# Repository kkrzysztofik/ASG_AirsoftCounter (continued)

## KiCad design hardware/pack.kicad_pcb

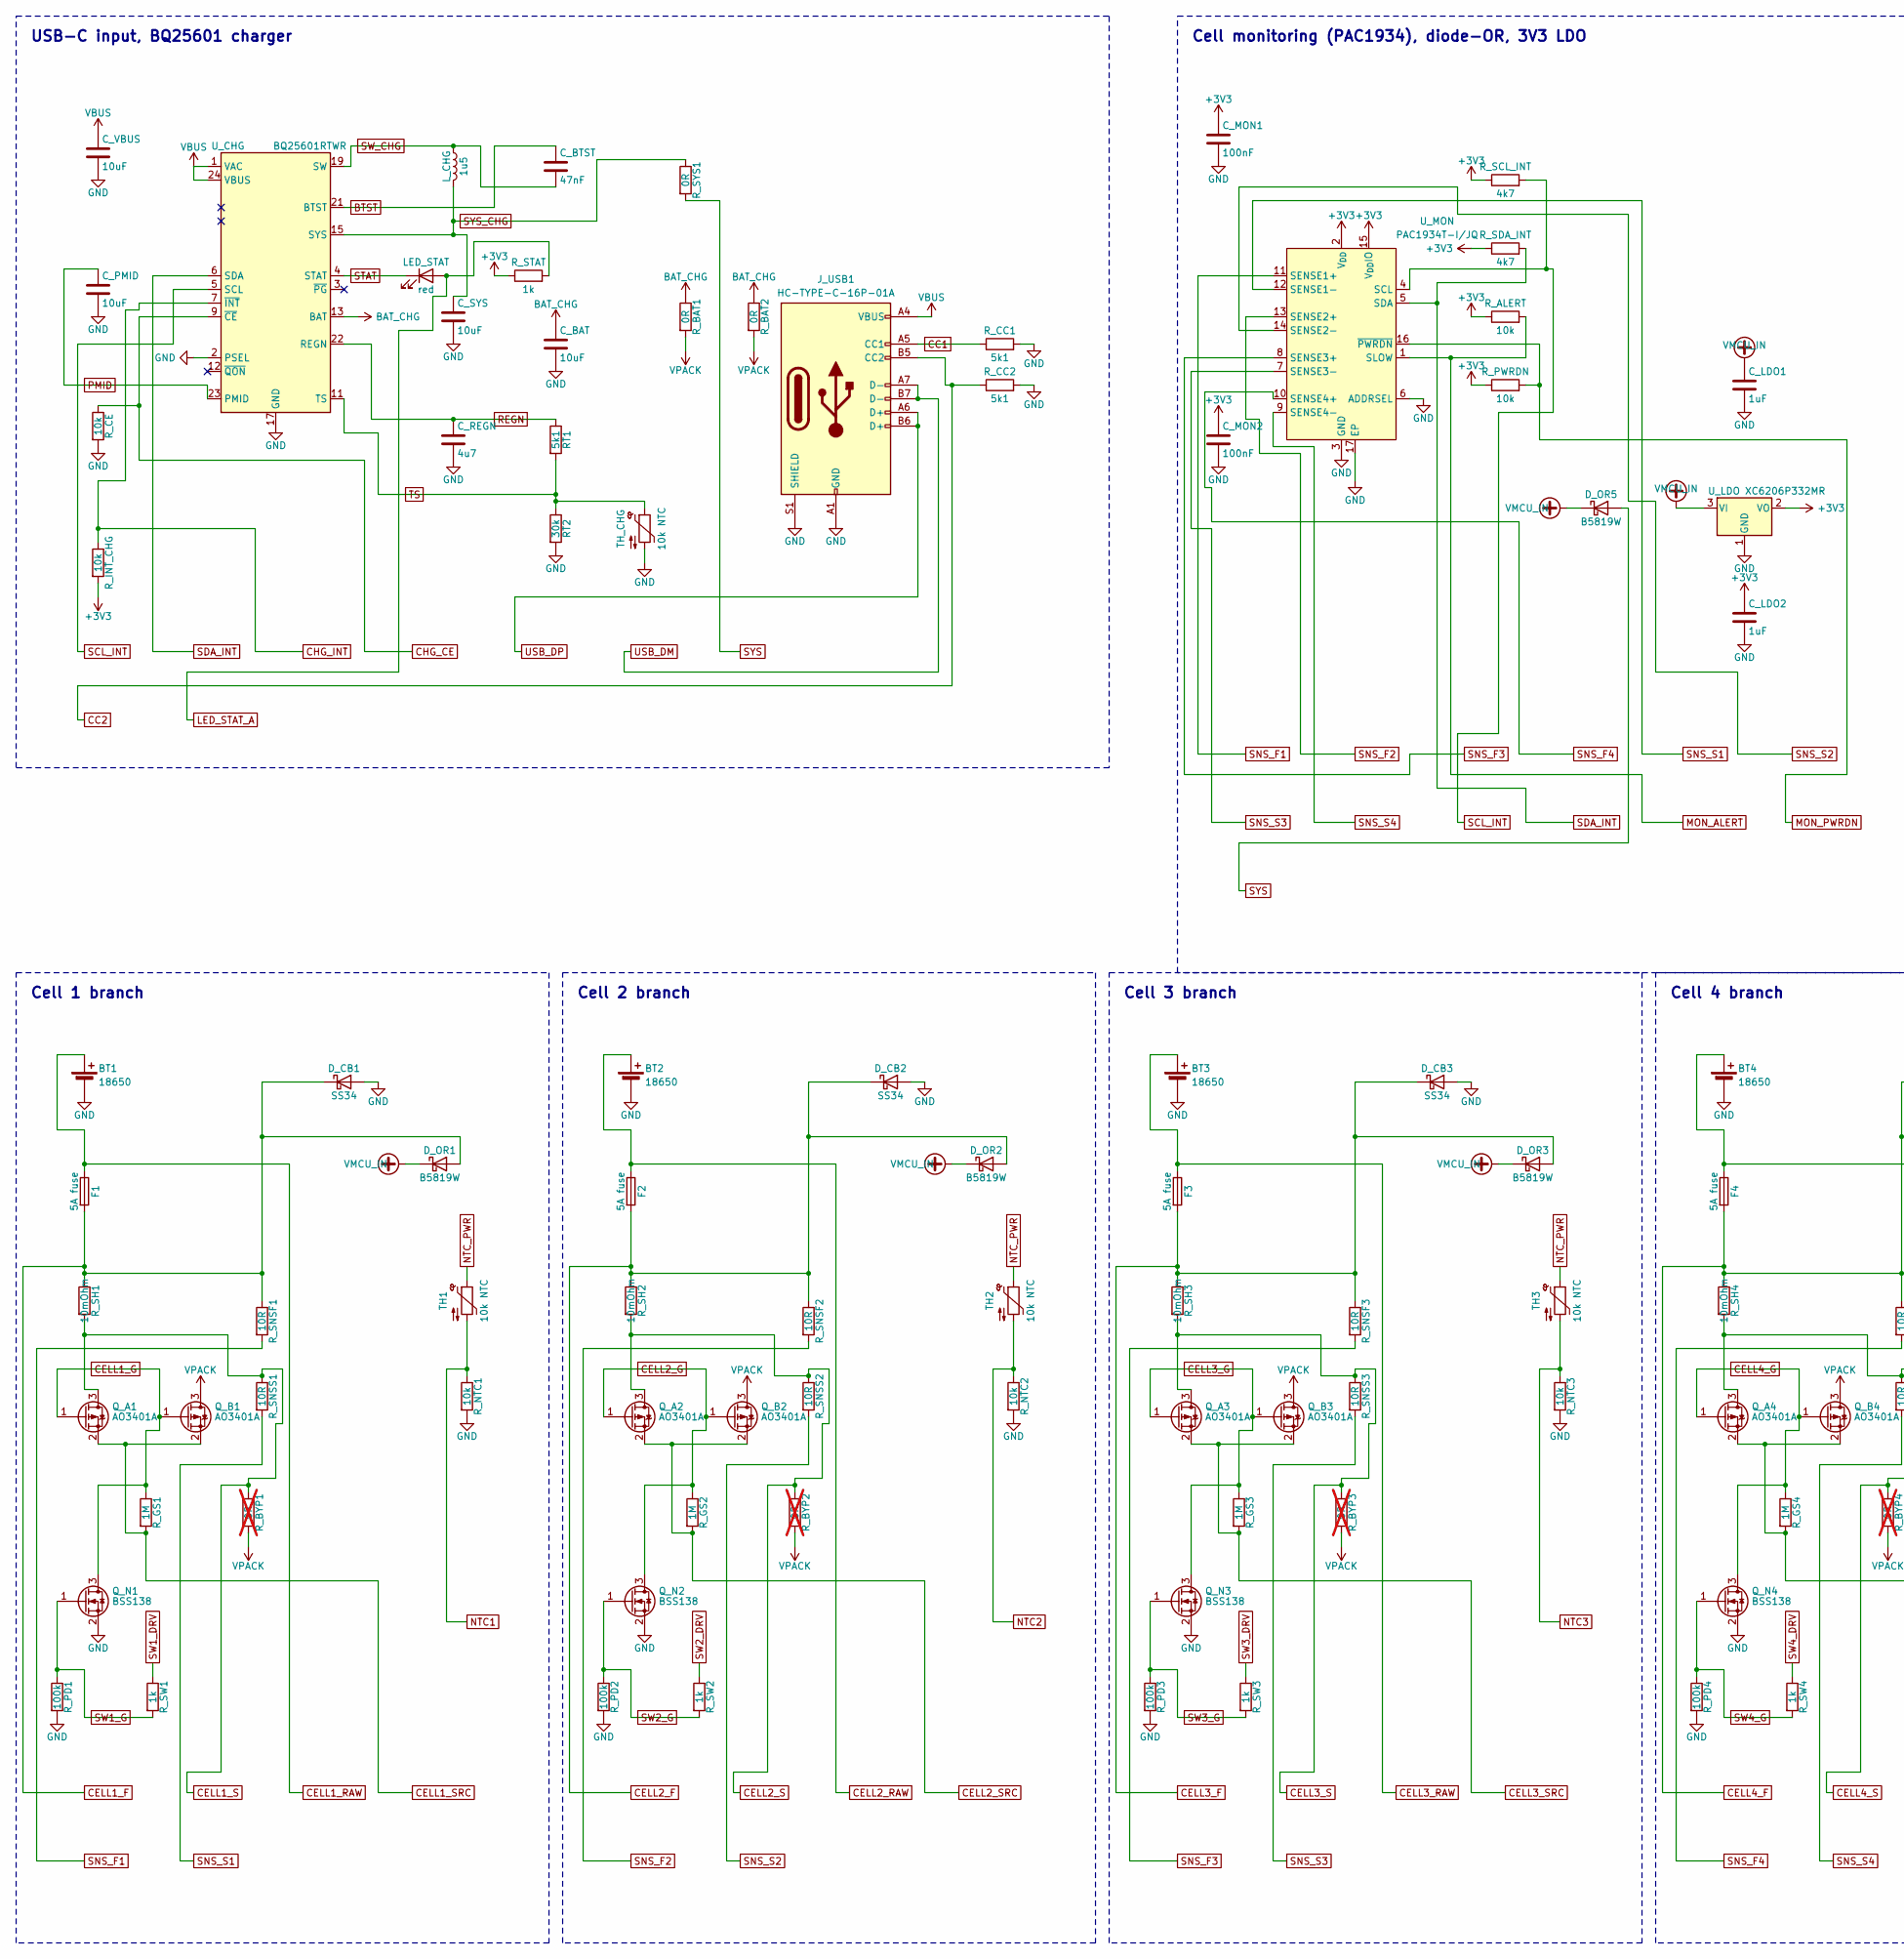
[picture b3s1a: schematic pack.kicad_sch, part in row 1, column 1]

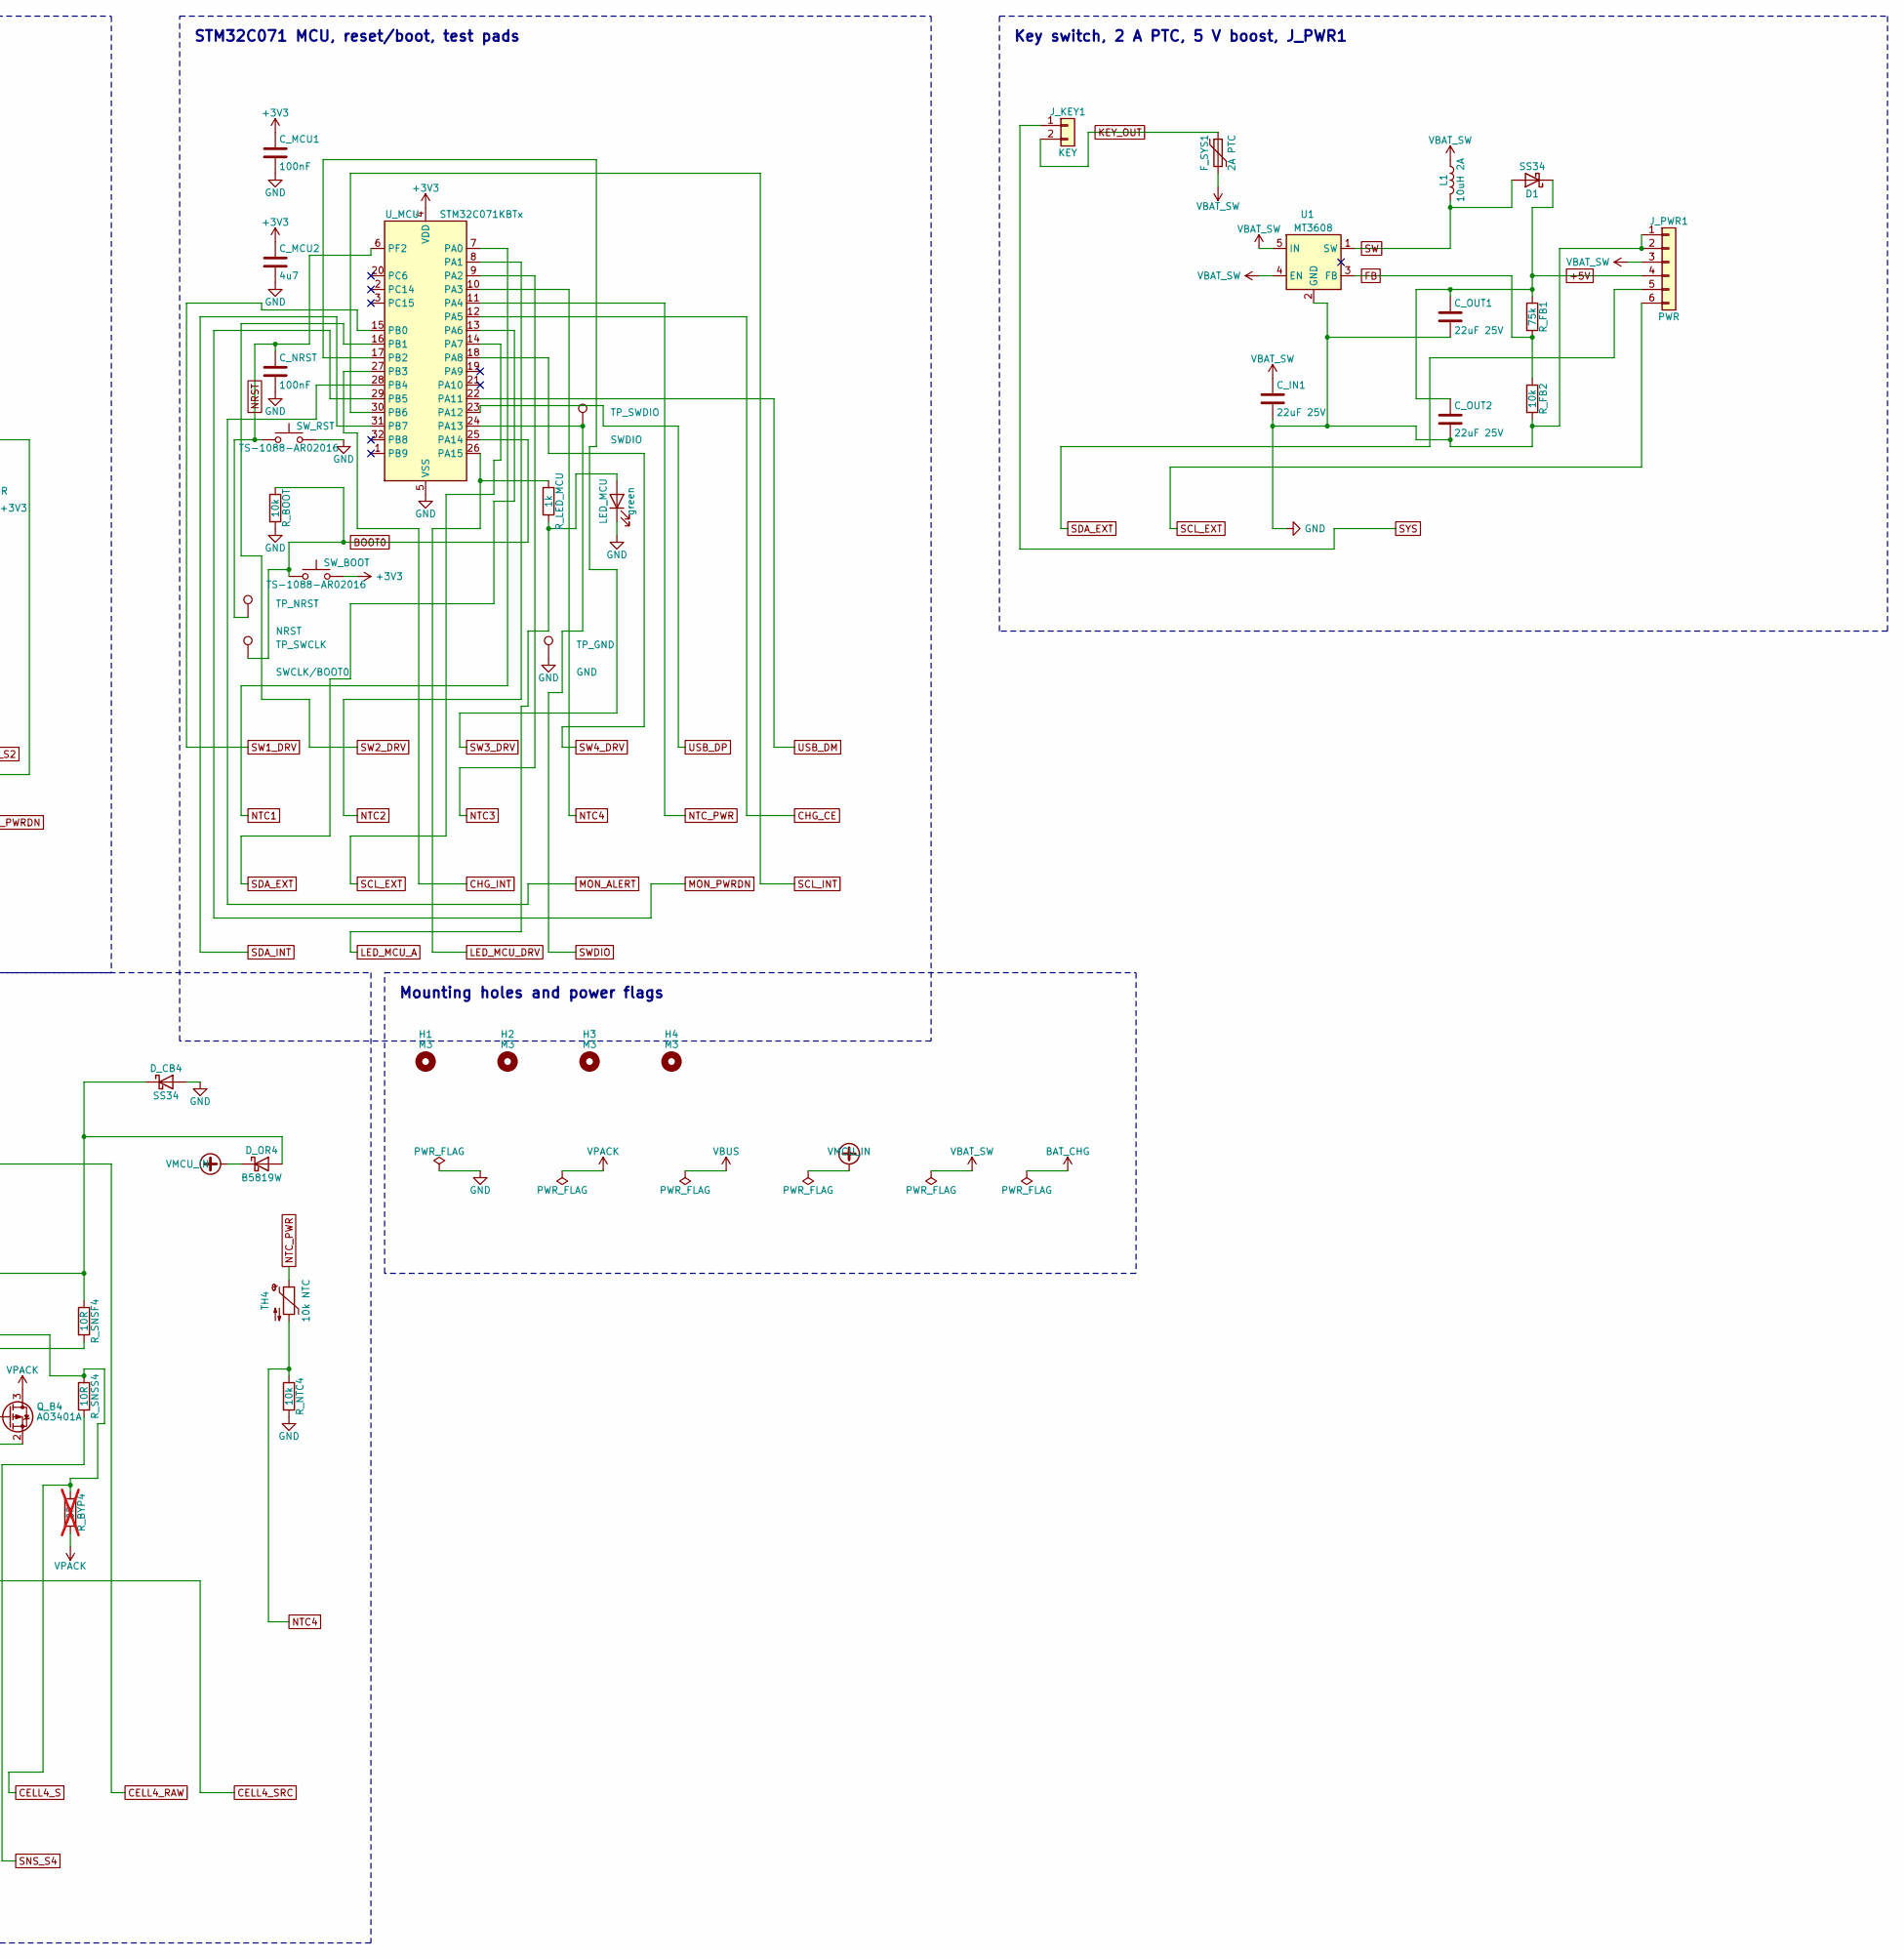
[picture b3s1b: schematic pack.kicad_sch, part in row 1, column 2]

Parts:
BT1, BT2, BT3, BT4: 18650; BatteryHolder_MYOUNG_BH-18650-A6AJ012
C_BAT: 10uF; C_0805_2012Metric_Pad1.18x1.45mm_HandSolder
C_BTST: 47nF; C_0805_2012Metric_Pad1.18x1.45mm_HandSolder
C_IN1: 22uF 25V; C_1206_3216Metric_Pad1.33x1.80mm_HandSolder
C_LDO1, C_LDO2: 1uF; C_0805_2012Metric_Pad1.18x1.45mm_HandSolder
C_MCU1: 100nF; C_0805_2012Metric_Pad1.18x1.45mm_HandSolder
C_MCU2: 4u7; C_0805_2012Metric_Pad1.18x1.45mm_HandSolder
C_MON1, C_MON2: 100nF; C_0805_2012Metric_Pad1.18x1.45mm_HandSolder
C_NRST: 100nF; C_0805_2012Metric_Pad1.18x1.45mm_HandSolder
C_OUT1, C_OUT2: 22uF 25V; C_1206_3216Metric_Pad1.33x1.80mm_HandSolder
C_PMID: 10uF; C_0805_2012Metric_Pad1.18x1.45mm_HandSolder
C_REGN: 4u7; C_0805_2012Metric_Pad1.18x1.45mm_HandSolder
C_SYS: 10uF; C_0805_2012Metric_Pad1.18x1.45mm_HandSolder
C_VBUS: 10uF; C_0805_2012Metric_Pad1.18x1.45mm_HandSolder
D1: SS34; D_SMA
D_CB1, D_CB2, D_CB3, D_CB4: SS34; D_SMA
D_OR1, D_OR2, D_OR3, D_OR4, D_OR5: B5819W; D_SOD-123
F1, F2, F3, F4: 5A fuse; Fuse_1206_3216Metric_Pad1.42x1.75mm_HandSolder
F_SYS1: 2A PTC; Fuse_1206_3216Metric_Pad1.42x1.75mm_HandSolder
H1, H2, H3, H4: M3; MountingHole_3.2mm_M3
J_KEY1: KEY; JST_XH_B2B-XH-A_1x02_P2.50mm_Vertical
J_PWR1: PWR; JST_XH_B6B-XH-A_1x06_P2.50mm_Vertical
J_USB1: HC-TYPE-C-16P-01A; USB_C_Receptacle_HCTL_HC-TYPE-C-16P-01A
L1: 10uH 2A; L_Bourns_SRN6045TA
LED_MCU: green; LED_0805_2012Metric_Pad1.15x1.40mm_HandSolder
LED_STAT: red; LED_0805_2012Metric_Pad1.15x1.40mm_HandSolder
L_CHG: 1u5; L_1210_3225Metric_Pad1.42x2.65mm_HandSolder
Q_A1, Q_A2, Q_A3, Q_A4: AO3401A; SOT-23
Q_B1, Q_B2, Q_B3, Q_B4: AO3401A; SOT-23
Q_N1, Q_N2, Q_N3, Q_N4: BSS138; SOT-23
RT1: 5k1; R_0805_2012Metric_Pad1.20x1.40mm_HandSolder
RT2: 30k; R_0805_2012Metric_Pad1.20x1.40mm_HandSolder
R_ALERT: 10k; R_0805_2012Metric_Pad1.20x1.40mm_HandSolder
R_BAT1, R_BAT2: 0R; R_1206_3216Metric_Pad1.30x1.75mm_HandSolder
R_BOOT: 10k; R_0805_2012Metric_Pad1.20x1.40mm_HandSolder
R_BYP1, R_BYP2, R_BYP3, R_BYP4: 0R; R_0805_2012Metric_Pad1.20x1.40mm_HandSolder; not fitted
R_CC1, R_CC2: 5k1; R_0805_2012Metric_Pad1.20x1.40mm_HandSolder
R_CE: 10k; R_0805_2012Metric_Pad1.20x1.40mm_HandSolder
R_FB1: 75k; R_0805_2012Metric_Pad1.20x1.40mm_HandSolder
R_FB2: 10k; R_0805_2012Metric_Pad1.20x1.40mm_HandSolder
R_GS1, R_GS2, R_GS3, R_GS4: 1M; R_0805_2012Metric_Pad1.20x1.40mm_HandSolder
R_INT_CHG: 10k; R_0805_2012Metric_Pad1.20x1.40mm_HandSolder
R_LED_MCU: 1k; R_0805_2012Metric_Pad1.20x1.40mm_HandSolder
R_NTC1, R_NTC2, R_NTC3, R_NTC4: 10k; R_0805_2012Metric_Pad1.20x1.40mm_HandSolder
R_PD1, R_PD2, R_PD3, R_PD4: 100k; R_0805_2012Metric_Pad1.20x1.40mm_HandSolder
R_PWRDN: 10k; R_0805_2012Metric_Pad1.20x1.40mm_HandSolder
R_SCL_INT: 4k7; R_0805_2012Metric_Pad1.20x1.40mm_HandSolder
R_SDA_INT: 4k7; R_0805_2012Metric_Pad1.20x1.40mm_HandSolder
R_SH1, R_SH2, R_SH3, R_SH4: 10mOhm; R_1206_3216Metric_Pad1.30x1.75mm_HandSolder
R_SNSF1, R_SNSF2, R_SNSF3, R_SNSF4: 10R; R_0805_2012Metric_Pad1.20x1.40mm_HandSolder
R_SNSS1, R_SNSS2, R_SNSS3, R_SNSS4: 10R; R_0805_2012Metric_Pad1.20x1.40mm_HandSolder
R_STAT: 1k; R_0805_2012Metric_Pad1.20x1.40mm_HandSolder
R_SW1, R_SW2, R_SW3, R_SW4: 1k; R_0805_2012Metric_Pad1.20x1.40mm_HandSolder
R_SYS1: 0R; R_1206_3216Metric_Pad1.30x1.75mm_HandSolder
SW_BOOT: TS-1088-AR02016; SW_SPST_TS-1088-xR020
SW_RST: TS-1088-AR02016; SW_SPST_TS-1088-xR020
TH1, TH2, TH3, TH4: 10k NTC; NTC_Bead_P2.54mm
TH_CHG: 10k NTC; R_0805_2012Metric_Pad1.20x1.40mm_HandSolder
TP_GND: GND; TestPoint_Pad_D1.5mm
TP_NRST: NRST; TestPoint_Pad_D1.5mm
TP_SWCLK: SWCLK/BOOT0; TestPoint_Pad_D1.5mm
TP_SWDIO: SWDIO; TestPoint_Pad_D1.5mm
U1: MT3608; SOT-23-6
U_CHG: BQ25601RTWR; QFN-24-1EP_4x4mm_P0.5mm_EP2.6x2.6mm
U_LDO: XC6206P332MR; SOT-23-3
U_MCU: STM32C071KBTx; LQFP-32_7x7mm_P0.8mm
U_MON: PAC1934T-I/JQ; UQFN-16-1EP_4x4mm_P0.65mm_EP2.6x2.6mm

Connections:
+3V3: C_LDO2.1, C_MCU1.1, C_MCU2.1, C_MON1.1, C_MON2.1, R_ALERT.1, R_INT_CHG.2, R_PWRDN.1, R_SCL_INT.1, R_SDA_INT.1, R_STAT.1, SW_BOOT.2, U_LDO.2 (VO), U_MCU.4 (VDD), U_MON.2 (V_{DD}), U_MON.15 (V_{DD}IO)
+5V: C_OUT1.1, C_OUT2.1, D1.1 (K), J_PWR1.4, R_FB1.1
BAT_CHG: C_BAT.1, R_BAT1.1, R_BAT2.1, U_CHG.13 (BAT), U_CHG.14 (BAT)
BOOT0: R_BOOT.1, SW_BOOT.1, TP_SWCLK.1, U_MCU.25 (PA14)
BTST: C_BTST.1, U_CHG.21 (BTST)
CC1: J_USB1.A5 (CC1), R_CC1.1
CC2: J_USB1.B5 (CC2), R_CC2.1
CELL1_F: D_CB1.1 (K), D_OR1.2 (A), F1.2, R_SH1.1, R_SNSF1.1
CELL1_G: Q_A1.1 (G), Q_B1.1 (G), Q_N1.3 (D), R_GS1.1
CELL1_RAW: BT1.1 (+), F1.1
CELL1_S: Q_A1.3 (D), R_BYP1.1, R_SH1.2, R_SNSS1.1
CELL1_SRC: Q_A1.2 (S), Q_B1.2 (S), R_GS1.2
CELL2_F: D_CB2.1 (K), D_OR2.2 (A), F2.2, R_SH2.1, R_SNSF2.1
CELL2_G: Q_A2.1 (G), Q_B2.1 (G), Q_N2.3 (D), R_GS2.1
CELL2_RAW: BT2.1 (+), F2.1
CELL2_S: Q_A2.3 (D), R_BYP2.1, R_SH2.2, R_SNSS2.1
CELL2_SRC: Q_A2.2 (S), Q_B2.2 (S), R_GS2.2
CELL3_F: D_CB3.1 (K), D_OR3.2 (A), F3.2, R_SH3.1, R_SNSF3.1
CELL3_G: Q_A3.1 (G), Q_B3.1 (G), Q_N3.3 (D), R_GS3.1
CELL3_RAW: BT3.1 (+), F3.1
CELL3_S: Q_A3.3 (D), R_BYP3.1, R_SH3.2, R_SNSS3.1
CELL3_SRC: Q_A3.2 (S), Q_B3.2 (S), R_GS3.2
CELL4_F: D_CB4.1 (K), D_OR4.2 (A), F4.2, R_SH4.1, R_SNSF4.1
CELL4_G: Q_A4.1 (G), Q_B4.1 (G), Q_N4.3 (D), R_GS4.1
CELL4_RAW: BT4.1 (+), F4.1
CELL4_S: Q_A4.3 (D), R_BYP4.1, R_SH4.2, R_SNSS4.1
CELL4_SRC: Q_A4.2 (S), Q_B4.2 (S), R_GS4.2
CHG_CE: R_CE.1, U_CHG.9 (~CE), U_MCU.12 (PA5)
CHG_INT: R_INT_CHG.1, U_CHG.7 (~INT), U_MCU.27 (PB3)
FB: R_FB1.2, R_FB2.1, U1.3 (FB)
GND: BT1.2 (-), BT2.2 (-), BT3.2 (-), BT4.2 (-), C_BAT.2, C_IN1.2, C_LDO1.2, C_LDO2.2, C_MCU1.2, C_MCU2.2, C_MON1.2, C_MON2.2, C_NRST.2, C_OUT1.2, C_OUT2.2, C_PMID.2, C_REGN.2, C_SYS.2, C_VBUS.2, D_CB1.2 (A), D_CB2.2 (A), D_CB3.2 (A), D_CB4.2 (A), J_PWR1.1, J_PWR1.2, J_USB1.A1 (GND), J_USB1.A12 (GND), J_USB1.B1 (GND), J_USB1.B12 (GND), J_USB1.S1 (SHIELD), LED_MCU.1 (K), Q_N1.2 (S), Q_N2.2 (S), Q_N3.2 (S), Q_N4.2 (S), RT2.2, R_BOOT.2, R_CC1.2, R_CC2.2, R_CE.2, R_FB2.2, R_NTC1.2, R_NTC2.2, R_NTC3.2, R_NTC4.2, R_PD1.2, R_PD2.2, R_PD3.2, R_PD4.2, SW_RST.2, TH_CHG.2, TP_GND.1, U1.2 (GND), U_CHG.2 (PSEL), U_CHG.17 (GND), U_CHG.18 (GND), U_CHG.25 (GND), U_LDO.1 (GND), U_MCU.5 (VSS), U_MON.3 (GND), U_MON.6 (ADDRSEL), U_MON.17 (EP)
KEY_OUT: F_SYS1.1, J_KEY1.2
LED_MCU_A: LED_MCU.2 (A), R_LED_MCU.2
LED_MCU_DRV: R_LED_MCU.1, U_MCU.26 (PA15)
LED_STAT_A: LED_STAT.2 (A), R_STAT.2
MON_ALERT: R_ALERT.2, U_MCU.28 (PB4), U_MON.1 (SLOW)
MON_PWRDN: R_PWRDN.2, U_MCU.29 (PB5), U_MON.16 (~PWRDN)
NRST: C_NRST.1, SW_RST.1, TP_NRST.1, U_MCU.6 (PF2)
NTC1: R_NTC1.1, TH1.2, U_MCU.7 (PA0)
NTC2: R_NTC2.1, TH2.2, U_MCU.8 (PA1)
NTC3: R_NTC3.1, TH3.2, U_MCU.9 (PA2)
NTC4: R_NTC4.1, TH4.2, U_MCU.10 (PA3)
NTC_PWR: TH1.1, TH2.1, TH3.1, TH4.1, U_MCU.11 (PA4)
PMID: C_PMID.1, U_CHG.23 (PMID)
REGN: C_REGN.1, RT1.1, U_CHG.22 (REGN)
SCL_EXT: J_PWR1.6, U_MCU.14 (PA7)
SCL_INT: R_SCL_INT.2, U_CHG.5 (SCL), U_MCU.30 (PB6), U_MON.4 (SCL)
SDA_EXT: J_PWR1.5, U_MCU.13 (PA6)
SDA_INT: R_SDA_INT.2, U_CHG.6 (SDA), U_MCU.31 (PB7), U_MON.5 (SDA)
SNS_F1: R_SNSF1.2, U_MON.11 (SENSE1+)
SNS_F2: R_SNSF2.2, U_MON.13 (SENSE2+)
SNS_F3: R_SNSF3.2, U_MON.8 (SENSE3+)
SNS_F4: R_SNSF4.2, U_MON.10 (SENSE4+)
SNS_S1: R_SNSS1.2, U_MON.12 (SENSE1-)
SNS_S2: R_SNSS2.2, U_MON.14 (SENSE2-)
SNS_S3: R_SNSS3.2, U_MON.7 (SENSE3-)
SNS_S4: R_SNSS4.2, U_MON.9 (SENSE4-)
STAT: LED_STAT.1 (K), U_CHG.4 (STAT)
SW: D1.2 (A), L1.2, U1.1 (SW)
SW1_DRV: R_SW1.1, U_MCU.15 (PB0)
SW1_G: Q_N1.1 (G), R_PD1.1, R_SW1.2
SW2_DRV: R_SW2.1, U_MCU.16 (PB1)
SW2_G: Q_N2.1 (G), R_PD2.1, R_SW2.2
SW3_DRV: R_SW3.1, U_MCU.17 (PB2)
SW3_G: Q_N3.1 (G), R_PD3.1, R_SW3.2
SW4_DRV: R_SW4.1, U_MCU.18 (PA8)
SW4_G: Q_N4.1 (G), R_PD4.1, R_SW4.2
SWDIO: TP_SWDIO.1, U_MCU.24 (PA13)
SW_CHG: C_BTST.2, L_CHG.1, U_CHG.19 (SW), U_CHG.20 (SW)
SYS: D_OR5.2 (A), J_KEY1.1, R_SYS1.2
SYS_CHG: C_SYS.1, L_CHG.2, R_SYS1.1, U_CHG.15 (SYS), U_CHG.16 (SYS)
TS: RT1.2, RT2.1, TH_CHG.1, U_CHG.11 (TS)
USB_DM: J_USB1.A7 (D-), J_USB1.B7 (D-), U_MCU.22 (PA11)
USB_DP: J_USB1.A6 (D+), J_USB1.B6 (D+), U_MCU.23 (PA12)
VBAT_SW: C_IN1.1, F_SYS1.2, J_PWR1.3, L1.1, U1.4 (EN), U1.5 (IN)
VBUS: C_VBUS.1, J_USB1.A4 (VBUS), J_USB1.A9 (VBUS), J_USB1.B4 (VBUS), J_USB1.B9 (VBUS), U_CHG.1 (VAC), U_CHG.24 (VBUS)
VMCU_IN: C_LDO1.1, D_OR1.1 (K), D_OR2.1 (K), D_OR3.1 (K), D_OR4.1 (K), D_OR5.1 (K), U_LDO.3 (VI)
VPACK: Q_B1.3 (D), Q_B2.3 (D), Q_B3.3 (D), Q_B4.3 (D), R_BAT1.2, R_BAT2.2, R_BYP1.2, R_BYP2.2, R_BYP3.2, R_BYP4.2

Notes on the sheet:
USB-C input, BQ25601 charger
Cell monitoring (PAC1934), diode-OR, 3V3 LDO
STM32C071 MCU, reset/boot, test pads
Key switch, 2 A PTC, 5 V boost, J_PWR1
Cell 1 branch
Cell 2 branch
Cell 3 branch
Cell 4 branch
Mounting holes and power flags

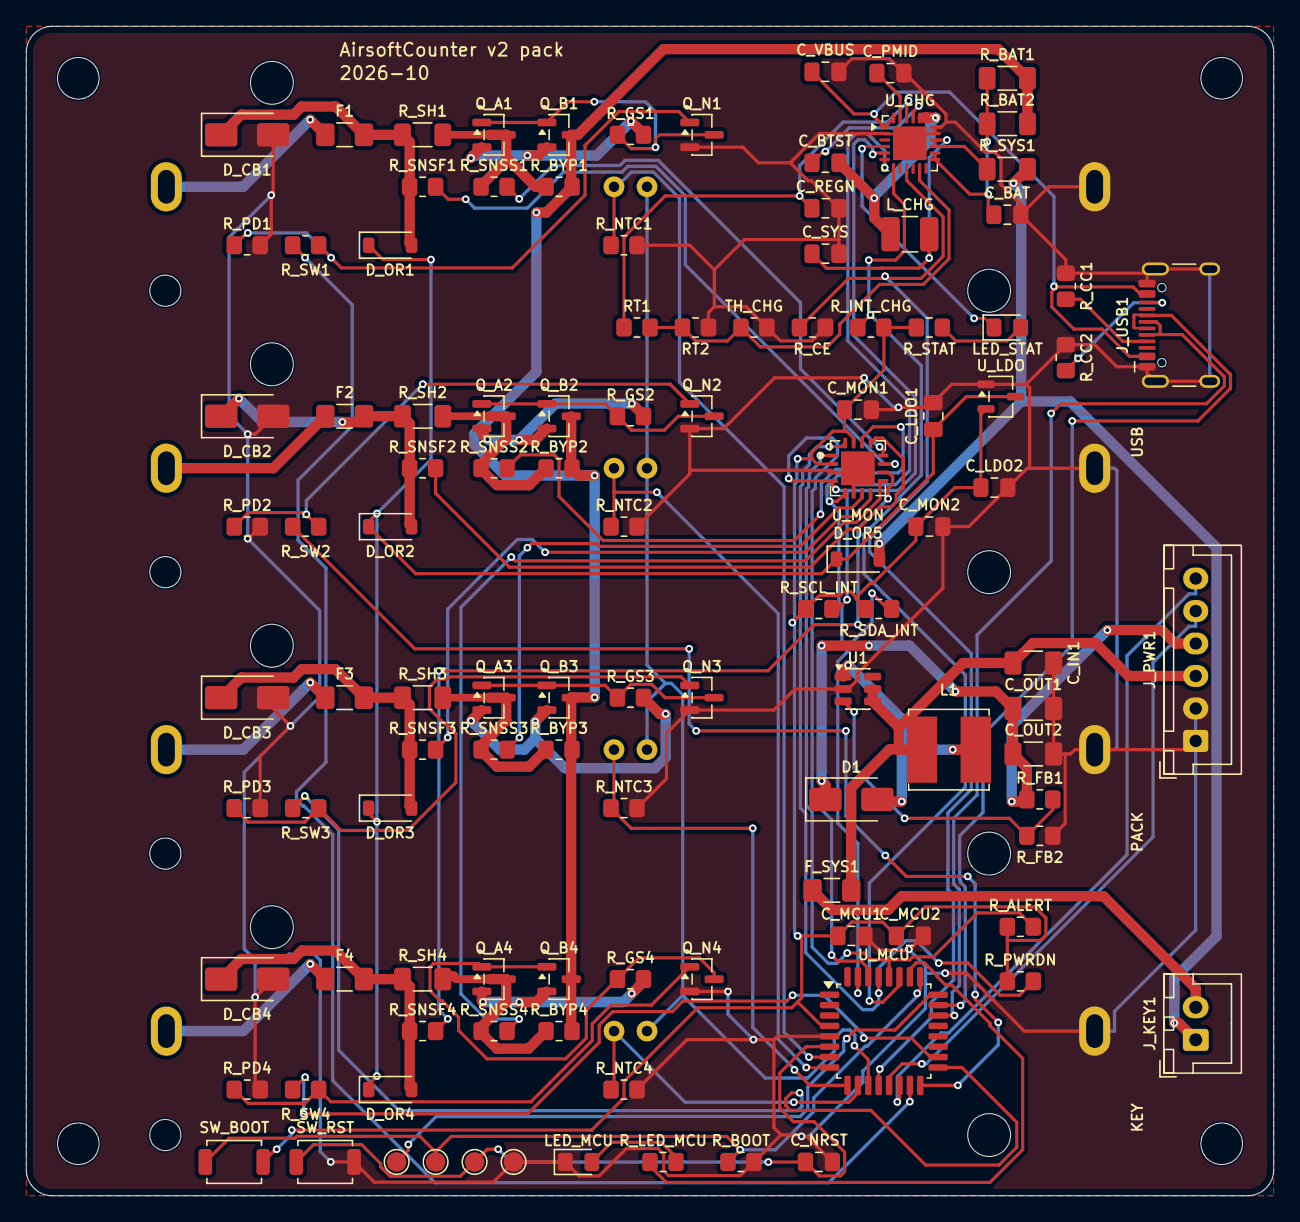
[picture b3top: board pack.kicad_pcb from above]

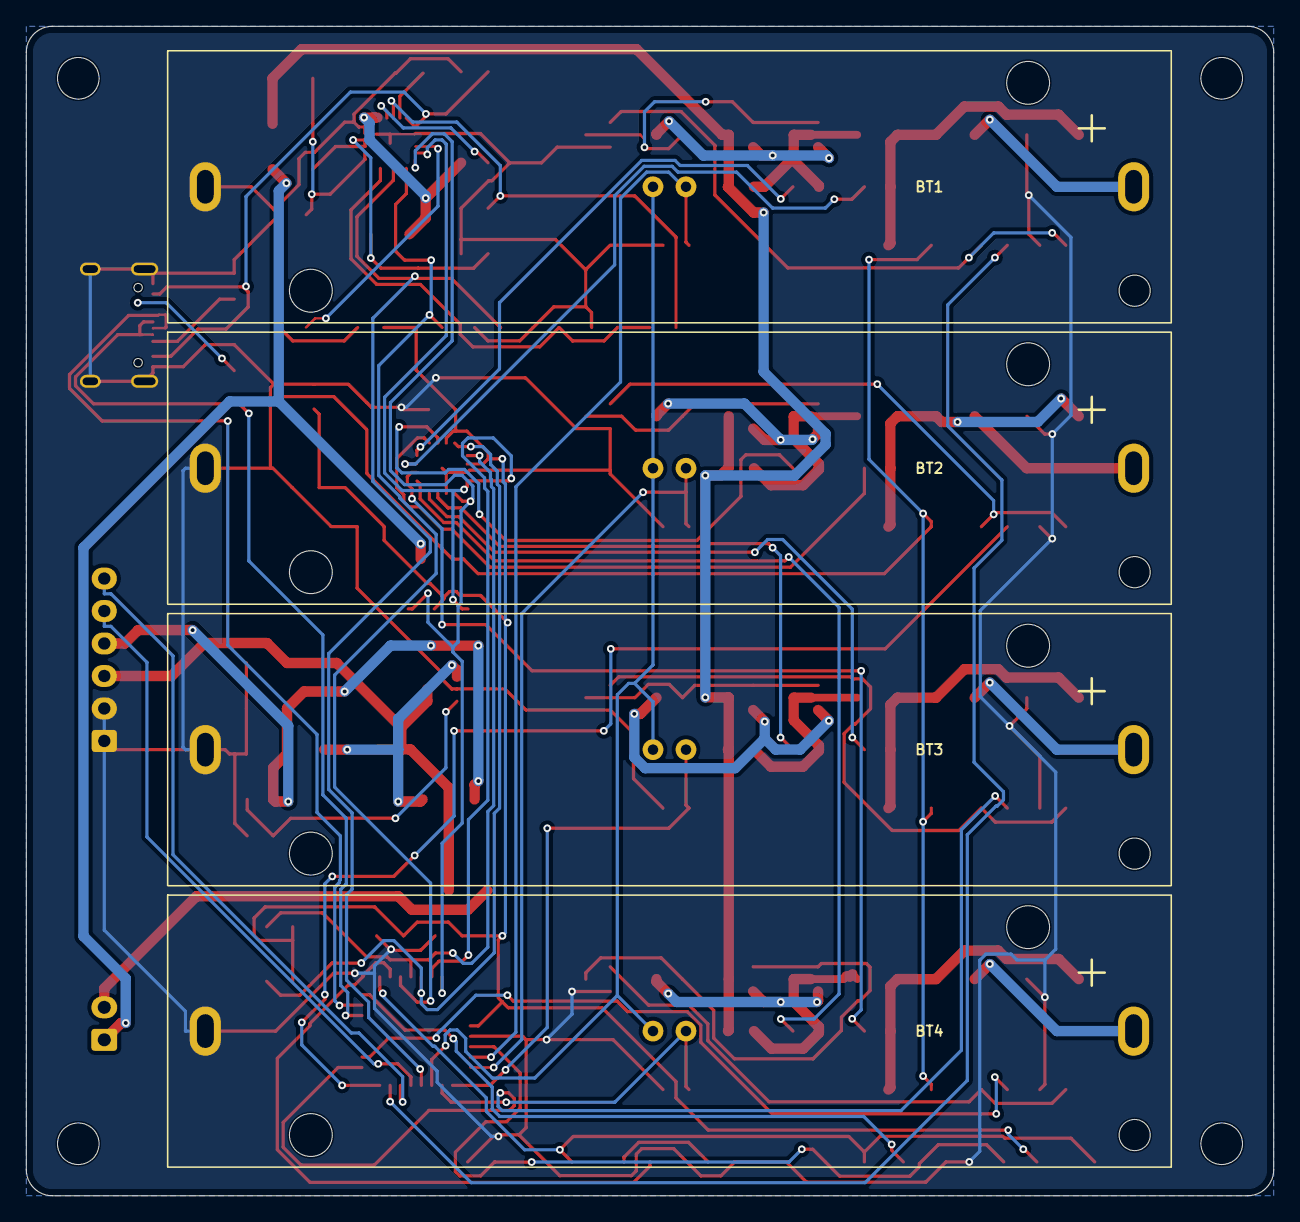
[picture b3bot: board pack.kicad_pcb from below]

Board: 2 copper layers, 96.0 x 90.0 mm, 124 parts (8 on the bottom side), 78 nets.
